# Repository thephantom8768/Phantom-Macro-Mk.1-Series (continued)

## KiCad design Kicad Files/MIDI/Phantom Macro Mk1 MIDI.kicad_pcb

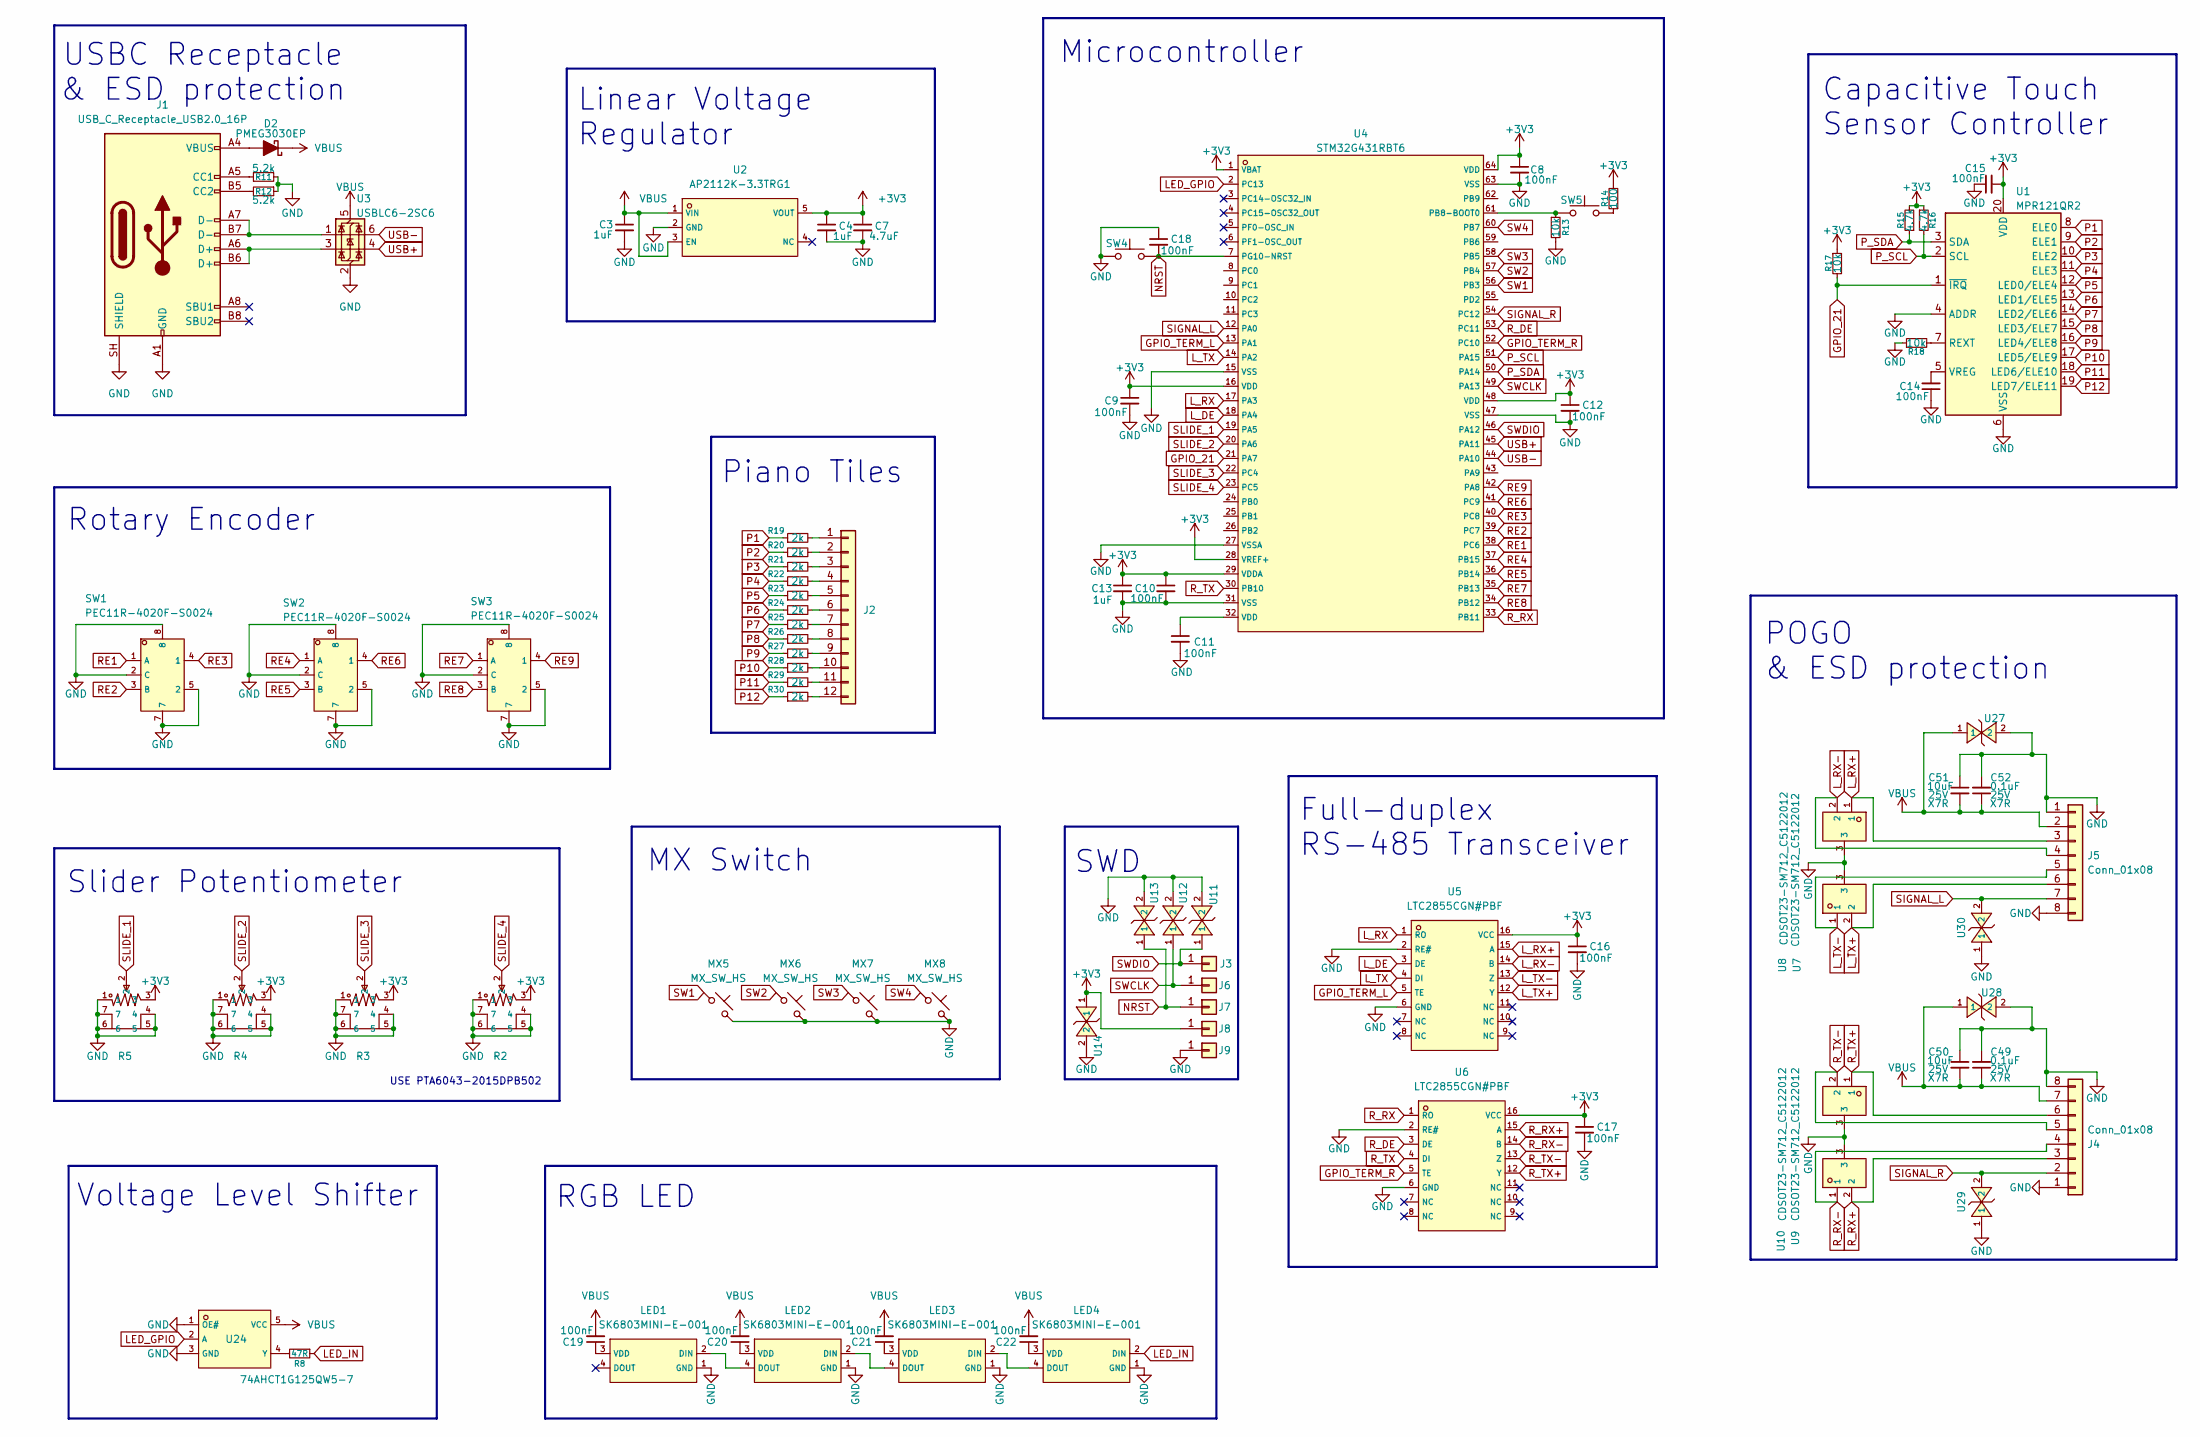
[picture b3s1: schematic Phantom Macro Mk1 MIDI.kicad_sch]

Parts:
C3, C4, C13: 1uF; C_0603_1608Metric_Pad1.08x0.95mm_HandSolder
C7: 4.7uF; C_0805_2012Metric_Pad1.18x1.45mm_HandSolder
C8, C9, C10, C11, C12, C14, C15, C16, C17, C18, C19, C20, C21, C22: 100nF; C_0402_1005Metric_Pad0.74x0.62mm_HandSolder
C49, C52: 0.1uF; C_0805_2012Metric_Pad1.18x1.45mm_HandSolder; Rating 25V
C50, C51: 10uF; C_0805_2012Metric_Pad1.18x1.45mm_HandSolder; Rating 25V
D2: PMEG3030EP; D_SOD-128
J1: USB_C_Receptacle_USB2.0_16P; USB_C_Receptacle_GCT_USB4110
J2: Conn_01x12; 7 key piano tiles
J3, J6, J7, J8, J9: Conn_01x01; PinSocket_1x01_P2.54mm_Vertical
J4, J5: Conn_01x08; PinHeader_1x08_P2.54mm_Horizontal
LED1, LED2, LED3, LED4: SK6803MINI-E-001; C5242955_LED-SMD_4P-L3_2-W2_8_SK6803MINI-E-001; LCSC C5242955
MX5, MX6, MX7, MX8: MX_SW_HS; SW_MX_HS_CPG151101S11_1u
R2, R3, R4, R5: PTA6043-2015DPA103; C17237498_RES-ADJ-TH_PTA6043-XXXX; LCSC C17237498
R8: 47R; R_0402_1005Metric_Pad0.72x0.64mm_HandSolder
R11, R12: 5.2k; R_0402_1005Metric_Pad0.72x0.64mm_HandSolder
R13, R17, R18: 10k; R_0402_1005Metric_Pad0.72x0.64mm_HandSolder
R14: 100; R_0402_1005Metric_Pad0.72x0.64mm_HandSolder
R15, R16: 4.7k; R_0402_1005Metric_Pad0.72x0.64mm_HandSolder
R19, R20, R21, R22, R23, R24, R25, R26, R27, R28, R29, R30: 2k; R_0402_1005Metric_Pad0.72x0.64mm_HandSolder
SW1, SW2, SW3: PEC11R-4020F-S0024; C143788_SW-TH_5P-L12_5-W13_4-P2_50-LS14_5; LCSC C143788
SW4, SW5: SW_Push; SW_SPST_B3U-1000P
U1: MPR121QR2; UQFN-20_3x3mm_P0.4mm
U2: AP2112K-3.3TRG1; C51118_SOT-25-5_L2_9-W1_6-P0_95-LS2_8-BL; LCSC C51118
U3: USBLC6-2SC6; SOT-23-6
U4: STM32G431RBT6; C431633_LQFP-64_L10_0-W10_0-P0_50-LS12_0-BL; LCSC C431633
U5, U6: LTC2855CGN#PBF; C682796_SSOP-16_L4_9-W3_9-P0_64-LS6_0-BL; LCSC C682796
U7, U8, U9, U10: CDSOT23-SM712_C5122012; C5122012_SOT-23-3_L2_9-W1_3-P0_95-LS2_4-BR; LCSC C5122012
U11, U12, U13, U14, U27, U28, U29, U30: TPD1E10B06DPYR; C48260_X1SON-2_L1_0-W0_6-P0_65-BI-1; LCSC C48260
U24: 74AHCT1G125QW5-7; C3755013_SOT-753_L3_1-W1_7-P0_95-LS3_0-BR; LCSC C3755013

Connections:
+3V3: C4.1, C7.1, C8.1, C9.1, C10.1, C12.1, C13.1, C15.2, C16.1, C17.1, J8.1 (Pin_1_1), R2.3, R3.3, R4.3, R5.3, R14.2, R15.2, R16.1, R17.1, U1.20 (VDD), U2.5 (VOUT), U4.1 (VBAT), U4.16 (VDD), U4.28 (VREF+), U4.29 (VDDA), U4.48 (VDD), U4.64 (VDD), U5.16 (VCC), U6.16 (VCC), U14.1
GND: C3.2, C4.2, C7.2, C8.2, C9.2, C10.2, C11.2, C12.2, C13.2, C14.1, C15.1, C16.2, C17.2, C18.1, C49.2, C50.1, C51.1, C52.2, J1.A1 (GND), J1.A12 (GND), J1.B1 (GND), J1.B12 (GND), J1.SH (SHIELD), J4.1, J4.8, J5.1, J5.8, J9.1 (Pin_1_1), LED1.1 (GND), LED2.1 (GND), LED3.1 (GND), LED4.1 (GND), MX5.2, MX6.2, MX7.2, MX8.2, R2.1, R2.4, R2.5, R2.6, R2.7, R3.1, R3.4, R3.5, R3.6, R3.7, R4.1, R4.4, R4.5, R4.6, R4.7, R5.1, R5.4, R5.5, R5.6, R5.7, R11.2, R12.1, R13.2, R18.1, SW1.2 (C), SW1.5 (2), SW1.7, SW1.8, SW2.2 (C), SW2.5 (2), SW2.7, SW2.8, SW3.2 (C), SW3.5 (2), SW3.7, SW3.8, SW4.1, U1.4 (ADDR), U1.6 (VSS), U2.2 (GND), U3.2 (GND), U4.15 (VSS), U4.27 (VSSA), U4.31 (VSS), U4.47 (VSS), U4.63 (VSS), U5.2 (RE#), U5.6 (GND), U6.2 (RE#), U6.6 (GND), U7.3, U8.3, U9.3, U10.3, U11.2, U12.2, U13.2, U14.2, U24.1 (OE#), U24.3 (GND), U27.2, U28.2, U29.1, U30.1
GPIO_21: R17.2, U1.1 (~IRQ), U4.21 (PA7)
GPIO_TERM_L: U4.13 (PA1), U5.5 (TE)
GPIO_TERM_R: U4.52 (PC10), U6.5 (TE)
LED_GPIO: U4.2 (PC13), U24.2 (A)
LED_IN: LED4.2 (DIN), R8.1
L_DE: U4.18 (PA4), U5.3 (DE)
L_RX: U4.17 (PA3), U5.1 (RO)
L_RX+: J5.3, U5.15 (A), U7.1
L_RX-: J5.4, U5.14 (B), U7.2
L_TX: U4.14 (PA2), U5.4 (DI)
L_TX+: J5.6, U5.12 (Y), U8.2
L_TX-: J5.5, U5.13 (Z), U8.1
NRST: C18.2, J7.1 (Pin_1_1), SW4.2, U4.7 (PG10-NRST), U13.1
unnamed: C11.1, U4.32 (VDD)
unnamed: D2.2 (A), J1.A4 (VBUS), J1.A9 (VBUS), J1.B4 (VBUS), J1.B9 (VBUS)
unnamed: J1.A5 (CC1), R11.1
unnamed: J1.B5 (CC2), R12.2
unnamed: J1.A6 (D+), J1.B6 (D+), U3.3 (I/O2)
unnamed: J1.A7 (D-), J1.B7 (D-), U3.1 (I/O1)
unnamed: J2.1, R19.2
unnamed: J2.2, R20.2
unnamed: J2.3, R21.2
unnamed: J2.4, R22.2
unnamed: J2.5, R23.2
unnamed: J2.6, R24.2
unnamed: J2.7, R25.2
unnamed: J2.8, R26.2
unnamed: J2.9, R27.2
unnamed: J2.10, R28.2
unnamed: J2.11, R29.2
unnamed: J2.12, R30.2
unnamed: LED1.2 (DIN), LED2.4 (DOUT)
unnamed: C19.1, LED1.3 (VDD)
unnamed: LED2.2 (DIN), LED3.4 (DOUT)
unnamed: C20.1, LED2.3 (VDD)
unnamed: LED3.2 (DIN), LED4.4 (DOUT)
unnamed: C21.1, LED3.3 (VDD)
unnamed: C22.1, LED4.3 (VDD)
unnamed: R14.1, SW5.2
unnamed: R18.2, U1.7 (REXT)
unnamed: C14.2, U1.5 (VREG)
unnamed: R13.1, SW5.1, U4.61 (PB8-BOOT0)
unnamed: R8.2, U24.4 (Y)
P1: R19.1, U1.8 (ELE0)
P2: R20.1, U1.9 (ELE1)
P3: R21.1, U1.10 (ELE2)
P4: R22.1, U1.11 (ELE3)
P5: R23.1, U1.12 (LED0/ELE4)
P6: R24.1, U1.13 (LED1/ELE5)
P7: R25.1, U1.14 (LED2/ELE6)
P8: R26.1, U1.15 (LED3/ELE7)
P9: R27.1, U1.16 (LED4/ELE8)
P10: R28.1, U1.17 (LED5/ELE9)
P11: R29.1, U1.18 (LED6/ELE10)
P12: R30.1, U1.19 (LED7/ELE11)
P_SCL: R16.2, U1.2 (SCL), U4.51 (PA15)
P_SDA: R15.1, U1.3 (SDA), U4.50 (PA14)
RE1: SW1.1 (A), U4.38 (PC6)
RE2: SW1.3 (B), U4.39 (PC7)
RE3: SW1.4 (1), U4.40 (PC8)
RE4: SW2.1 (A), U4.37 (PB15)
RE5: SW2.3 (B), U4.36 (PB14)
RE6: SW2.4 (1), U4.41 (PC9)
RE7: SW3.1 (A), U4.35 (PB13)
RE8: SW3.3 (B), U4.34 (PB12)
RE9: SW3.4 (1), U4.42 (PA8)
R_DE: U4.53 (PC11), U6.3 (DE)
R_RX: U4.33 (PB11), U6.1 (RO)
R_RX+: J4.3, U6.15 (A), U10.2
R_RX-: J4.4, U6.14 (B), U10.1
R_TX: U4.30 (PB10), U6.4 (DI)
R_TX+: J4.6, U6.12 (Y), U9.1
R_TX-: J4.5, U6.13 (Z), U9.2
SIGNAL_L: J5.7, U4.12 (PA0), U30.2
SIGNAL_R: J4.2, U4.54 (PC12), U29.2
SLIDE_1: R5.2, U4.19 (PA5)
SLIDE_2: R4.2, U4.20 (PA6)
SLIDE_3: R3.2, U4.22 (PC4)
SLIDE_4: R2.2, U4.23 (PC5)
SW1: MX5.1, U4.56 (PB3)
SW2: MX6.1, U4.57 (PB4)
SW3: MX7.1, U4.58 (PB5)
SW4: MX8.1, U4.60 (PB7)
SWCLK: J6.1 (Pin_1_1), U4.49 (PA13), U12.1
SWDIO: J3.1 (Pin_1_1), U4.46 (PA12), U11.1
USB+: U3.4 (I/O2), U4.45 (PA11)
USB-: U3.6 (I/O1), U4.44 (PA10)
VBUS: C3.1, C19.2, C20.2, C21.2, C22.2, C49.1, C50.2, C51.2, C52.1, D2.1 (K), J4.7, J5.2, U2.1 (VIN), U2.3 (EN), U3.5 (VBUS), U24.5 (VCC), U27.1, U28.1

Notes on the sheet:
Voltage Level Shifter
Full-duplex RS-485 Transceiver
MX Switch
Slider Potentiometer
Piano Tiles
USE PTA6043-2015DPB502
Microcontroller
POGO & ESD protection
Capacitive Touch Sensor Controller
SWD
RGB LED
Rotary Encoder
Linear Voltage Regulator
USBC Receptacle & ESD protection

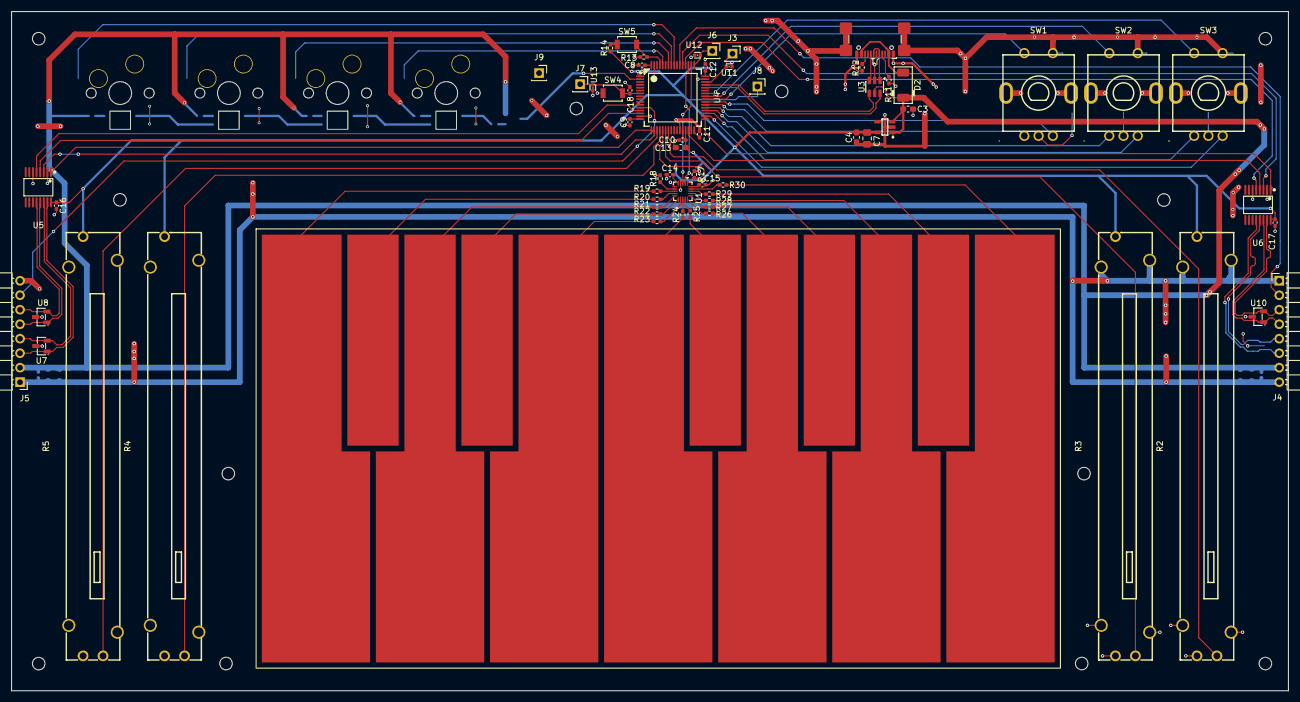
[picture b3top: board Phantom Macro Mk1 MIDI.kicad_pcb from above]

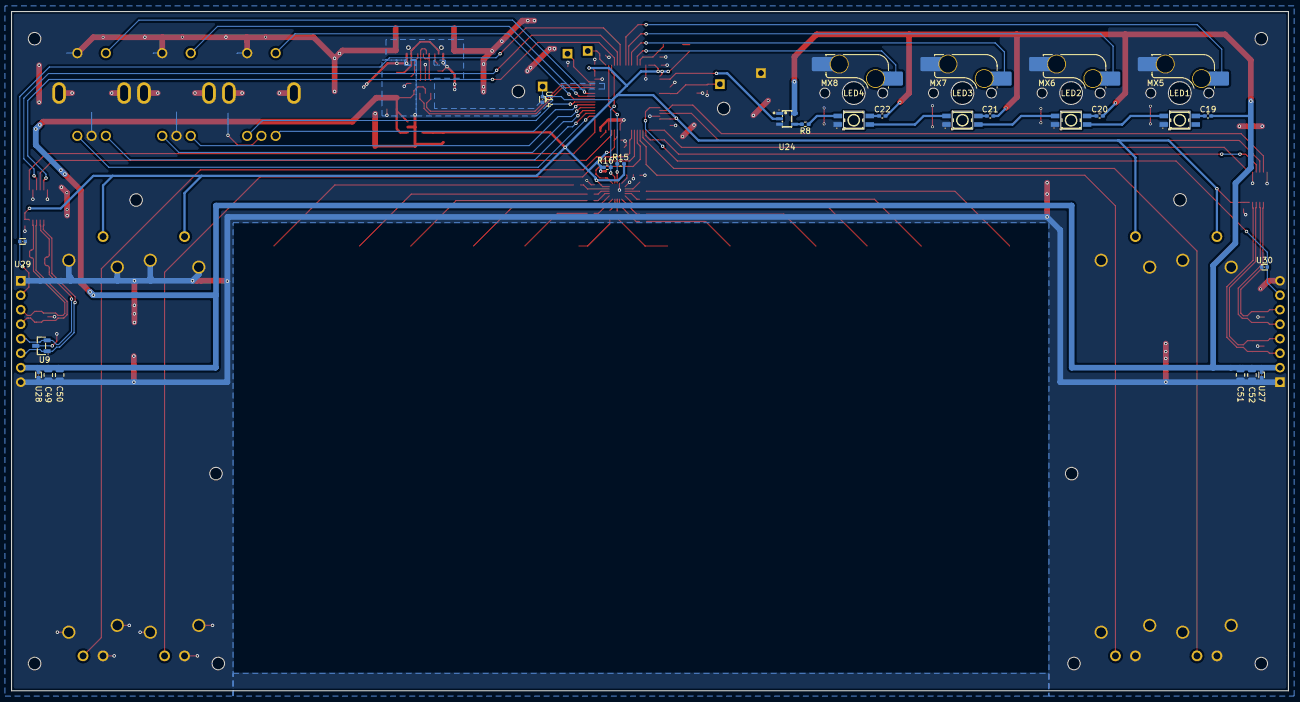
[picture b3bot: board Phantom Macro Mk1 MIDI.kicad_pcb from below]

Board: 2 copper layers, 223.8 x 119.1 mm, 89 parts (26 on the bottom side), 90 nets.
